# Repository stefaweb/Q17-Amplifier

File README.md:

# Q17 : A QUAD405 audiophile MOSFET amplifier
Q17 is an amplifier based on the QUAD405 current dumping principle.

The project for porting the operating principle of the QUAD405 to a MOSFET base was originally created by engineer Tiberiu Vicol.

Use KiCad to open and edit source files. The great KiCad software can be <a href="https://www.kicad.org/download/">downloaded</a> from CERN.

<b>Q17-Mini project 3.0 (90W @ 8 Ohms)</b>

The first version of the board was released on December 8, 2021.

Version 3.0.4 was published on October 7, 2024.

All files are located in Q17-Mini-3.0 directory. Old version are located in Q17-Mini Archives directory.

Q17-Mini v3.0 (95x75mm, 2 Oz PCB)

<b>Q17-TURBO project (150W @ 8 Ohms)</b>

The natural evolution of the Q17-Mini, this time with two pairs of power transistors, better thermal management, better technical characteristics and the same sound signature with more punch.

An amplifier that will warm up even the coldest speakers.

The first version of the board was released on January, 6 2023.

Version 2.0.1 was released on October 5, 2024.

All files are located in Q17-TURBO-2.0 directory. Old version are located in Q17-TURBO Archives directory.

Q17-TURBO v2.0 (190x75mm, 2 Oz PCB)

You can very simply manufacture your PCB via JLCPCB (https://jlcpcb.com) or PCBWay (https://www.pcbway.com) using the Gerber files available on this repository. You can also contact me, from time to time I have some spare copies of the Q17 PCBs that can be sold to you at cost price.

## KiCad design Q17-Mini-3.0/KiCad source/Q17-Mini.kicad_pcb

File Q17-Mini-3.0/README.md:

# Q17-Mini version 3.0 (90W @ 8 Ohms)</b><br>

<b>Technical specifications:</b>

THD: 0.011%<br>
SNR : 118 dB<br>
Intermodulation distortion: 0,2%<br>
Frequency response: ±0,1 dB<br>
Slew rate: 35 V/µs<br>
Damping factor : 350 with 1.2Vrms sensibility, 290 with 0.7Vrms sensibility<br>
Default gain: 22 with input gain at 1.2Vrms, 35 with input gain at 0.7Vrms.<br>
DC offset at output: 1mV with OPA1611, 0mV with OPA828.<br>
Power supply : 50Vdc<br>
Idle consumption: 9W

These measurements were made with amateur measuring equipment. It is better to take them as an indication than as safe values. 
<br>
<br>
The first version of the board was released on December 8, 2021.
<br>
<br>
Version 3.0.4 was published on October 7, 2024.

Read the CHANGELOG file to know what's new.

<a href="https://audio.cyberkata.org/Q17-Mini-3.0-BOM.html">Q17-Mini-3.0-BOM Online Version</a>
<br>
<br>
<a href="https://www.mouser.fr/ProjectManager/ProjectDetail.aspx?AccessID=dd2b71abab">Order Q17-Mini-3.0.4-BOM at Mouser</a><br> 
<br>

PCB size: 95 mm * 75 mm

Drilling for Q17-Mini

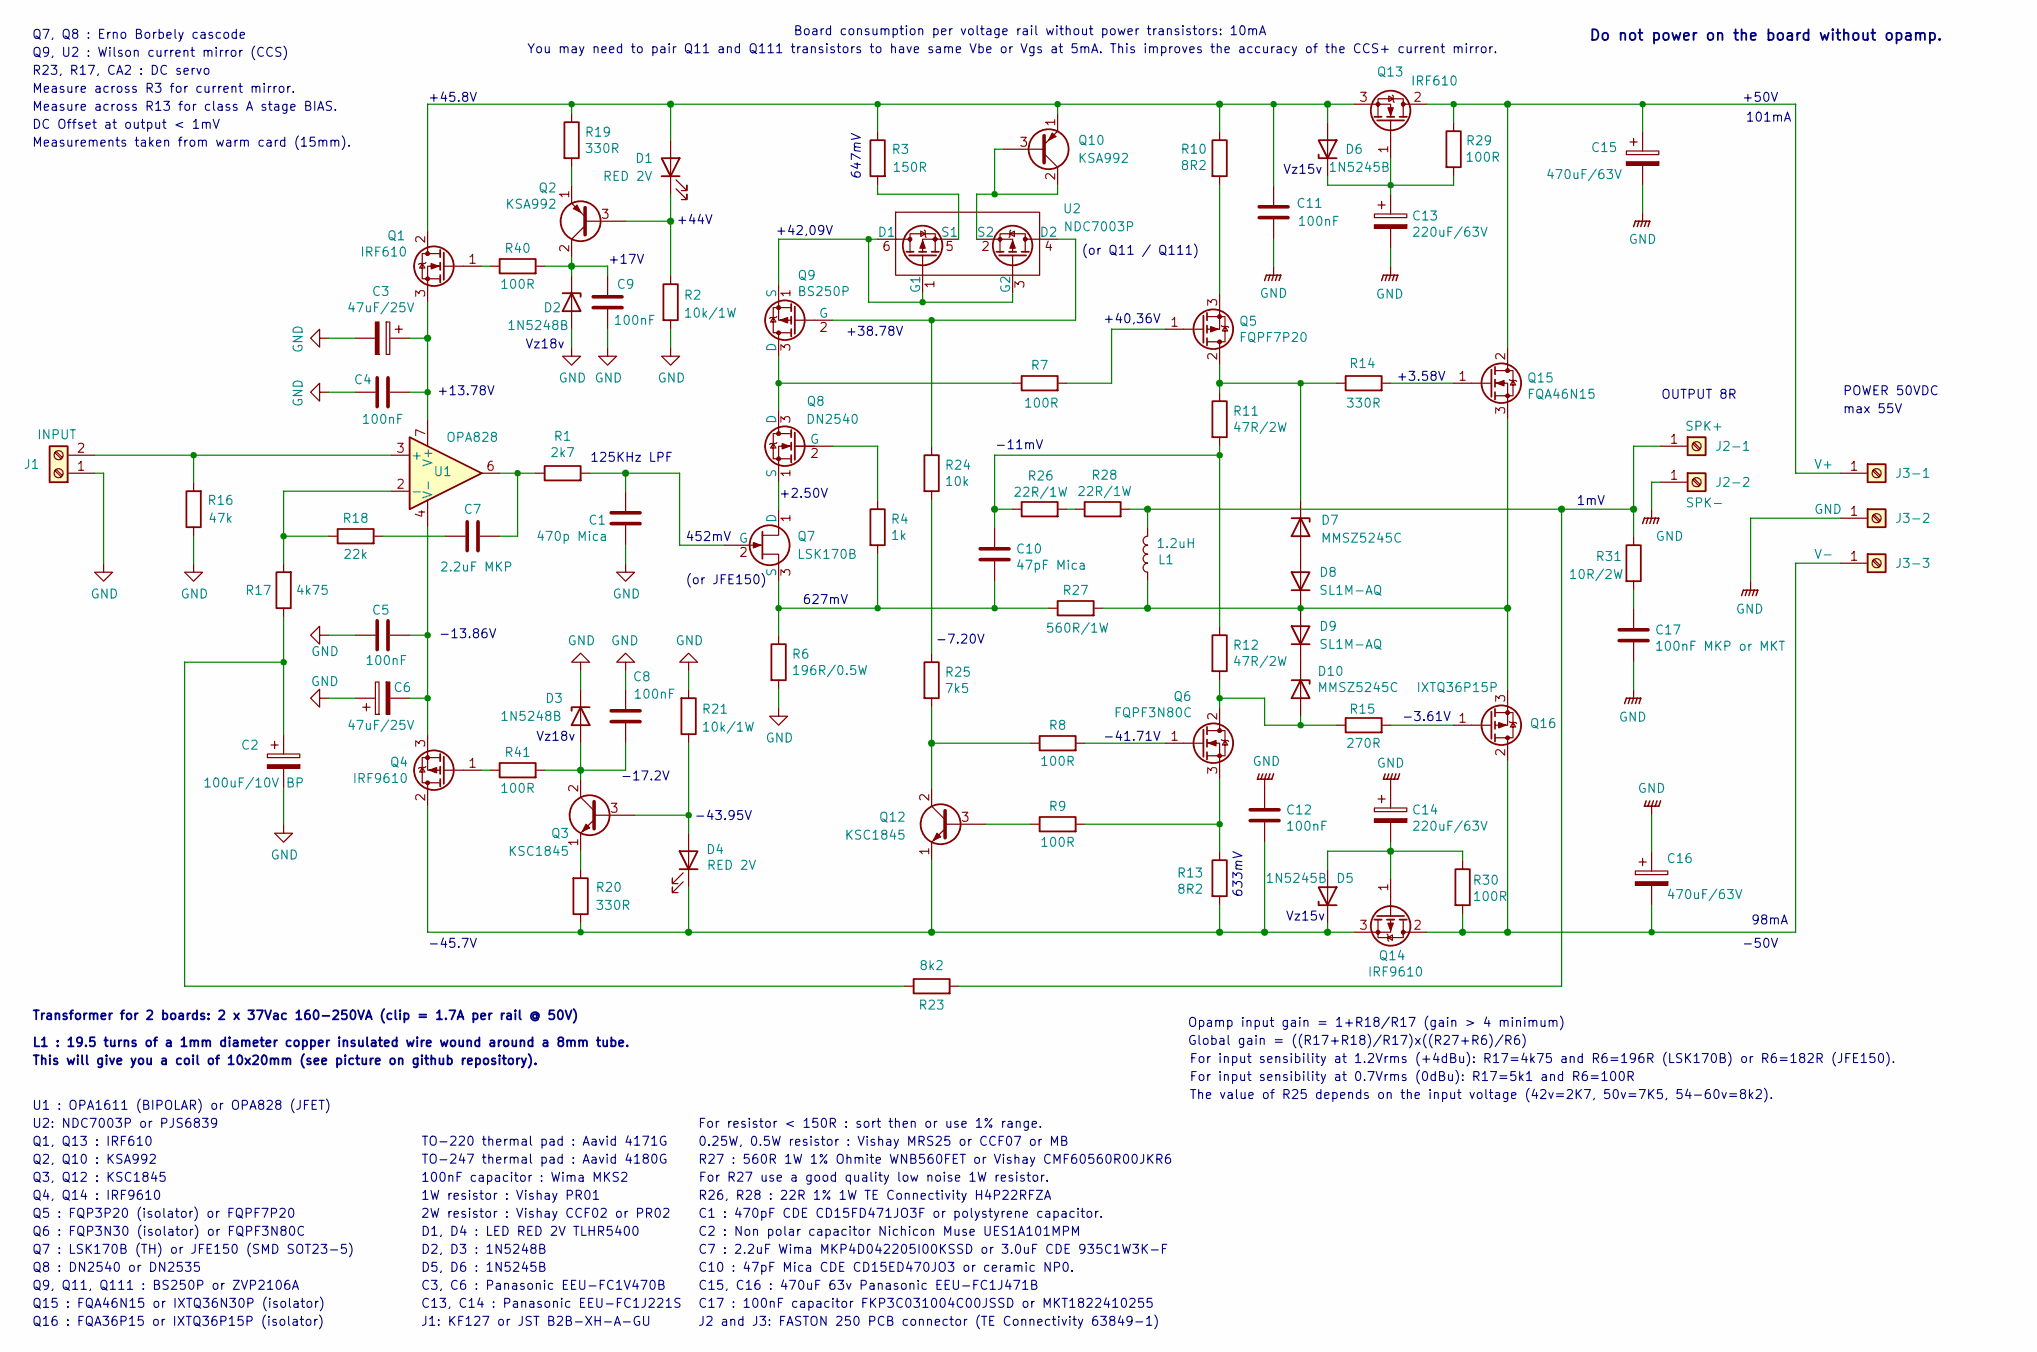
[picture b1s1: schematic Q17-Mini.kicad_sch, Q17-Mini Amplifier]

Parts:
C1: 470p Mica; C_Mica_v2_L11.4mm_W4.3mm_H9.1_P5.9mm_mix; Part# CD15FD471JO3; Mouser 5982-15-500V470
C2: 100uF/10V BP; CP_Radial_D10.0mm_P5.00mm; Part# UES1A101MPM; Mouser 647-UES1A101MPM
C3, C6: 47uF/25V; CP_Radial_D10.0mm_P2.50mm_P5.00mm; Part# EEU-FC1V470B; Mouser 667-EEU-FC1V470B
C4, C5, C8, C9, C11, C12: 100nF; C_Rect_L7.2mm_W2.5mm_P5.00mm_FKS2_FKP2_MKS2_MKP2; Part# MKS2D031001A00KSSD; Mouser 505-MKS2.1/100/10
C7: 2.2uF MKP; C_Rect_L26.5mm_W10.5mm_P22.50mm_MKS4; Part# MKP4D042205I00KSSD; Mouser 505-MKP4D042205I00KS
C10: 47pF Mica; C_Mica_v2_L11.4mm_W4.3mm_H9.1_P5.9mm_mix; Part# CD15ED470JO3F; Mouser 598-CD15ED470JO3F
C13, C14: 220uF/63V; CP_Radial_D12.5mm_P5.00mm; Part# EEU-FC1J221S; Mouser 667-EEU-FC1J221S
C15, C16: 470uF/63V; CP_Radial_D16.0mm_P7.50mm; Part# EEU-FC1J471B; Mouser 667-EEU-FC1J471B
C17: 100nF MKP or MKT; C_Rect_L18.0mm_W7.0mm_P15.00mm_FKS3_FKP3; Part# FKP3D031004D00JF00; Mouser 505-FKP3D03104D0JF0
D1, D4: RED 2V; LED_D5.0mm; Part# TLHR5400; Mouser 78-TLHR5400
D2, D3: 1N5248B; D_DO-35_SOD27_P7.62mm_Horizontal; Part# 1N5248B; Mouser 78-1N5248B
D5, D6: 1N5245B; D_DO-35_SOD27_P7.62mm_Horizontal; Part# 1N5245BTR; Mouser 512-1N5245BTR
D7, D10: MMSZ5245C; D_SOD-123; Part# MMSZ5245C-E3-18; Mouser 78-MMSZ5245C-E3-18
D8, D9: SL1M-AQ; D_SOD-123; Part# SL1M-AQ; Mouser 637-SL1M-AQ
J1: INPUT; Input_connector_mix_inverted; Part# Terminal Block Phoenix Contact 1755583; Mouser 651-1755583
J2-1: SPK+; Faston_Connector_63849-1_TEC; Part# TE Connectivity 63849-1; Mouser 571-638491
J2-2: SPK-; Faston_Connector_63849-1_TEC; Part# TE Connectivity 63849-1; Mouser 571-638491
J3-1: V+; Faston_Connector_63849-1_TEC; Part# TE Connectivity 63849-1; Mouser 571-638491
J3-2: GND; Faston_Connector_63849-1_TEC; Part# TE Connectivity 63849-1; Mouser 571-638491
J3-3: V-; Faston_Connector_63849-1_TEC; Part# TE Connectivity 63849-1; Mouser 571-638491
L1: 1.2uH; L_Axial_L22mm_D10mm_P21mm_vertical_Q17_Mini; Part# 19.5 turns of a 1mm diameter copper ins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; Mouser N.A
Q1, Q13: IRF610; TO-220-3_Vertical; Part# IRF610PBF; Mouser 844-IRF610PBF
Q2, Q10: KSA992; TO-92_Inline_Wide; Part# KSA992FTA; Mouser 512-KSA992FTA
Q3, Q12: KSC1845; TO-92_Inline_Wide; Part# KSC1845FTA; Mouser 512-KSC1845FTA
Q4, Q14: IRF9610; TO-220-3_Vertical; Part# IRF9610PBF; Mouser 844-IRF9610PBF
Q5: FQPF7P20; TO-220-3_Vertical; Part# FQPF7P20; Mouser 512-FQPF7P20
Q6: FQPF3N80C; TO-220-3_Vertical; Part# FQPF3N80C; Mouser 512-FQPF3N80C
Q7: LSK170B; TO-92_Inline_Wide; Part# LSK170B-TO-92-3L-BK; Mouser 722-LSK170BTO923LBK
Q8: DN2540; TO-92_Inline_Wide; Part# DN2540N3-G; Mouser 689-DN2540N3-G
Q9: BS250P; TO-92S_Wide; Part# BS250P; Mouser 522-BS250P
Q15: FQA46N15; TO-3P-3_Vertical; Part# FQA46N15; Mouser 512-FQA46N15
Q16: IXTQ36P15P; TO-3P-3_Vertical; Part# IXTQ36P15P; Mouser 747-IXTQ36P15P
R1: 2k7; R_Axial_DIN0207_L6.3mm_D2.5mm_P10.16mm_Horizontal; Part# MRS25000C2701FRP00; Mouser 594-MRS25000C2701FRP
R2, R21: 10k/1W; R_Axial_DIN0207_L6.3mm_D2.5mm_P10.16mm_Horizontal; Part# PR01000101002JR500; Mouser 594-5073NW10K00J
R3: 150R; R_Axial_DIN0207_L6.3mm_D2.5mm_P10.16mm_Horizontal; Part# MRS25000C1500FRP00; Mouser 594-MRS25000C1500FRP
R4: 1k; R_Axial_DIN0207_L6.3mm_D2.5mm_P10.16mm_Horizontal; Part# MRS25000C1001FRP00; Mouser 594-MRS25000C1001FRP
R6: 196R/0.5W; R_Axial_DIN0207_L6.3mm_D2.5mm_P10.16mm_Horizontal; Part# MRS25000C1960FCT00; Mouser 594-MRS25000C1960FCT
R7, R9, R29, R30, R40, R41: 100R; R_Axial_DIN0207_L6.3mm_D2.5mm_P10.16mm_Horizontal; Part# MRS25000C1000FCT00; Mouser 594-MRS25000C1000FCT
R8: 100R; R_Axial_DIN0207_L6.3mm_D2.5mm_P10.16mm_Horizontal; Part# MRS25000C1000FCT; Mouser 594-MRS25000C1000FCT
R10, R13: 8R2; R_Axial_DIN0207_L6.3mm_D2.5mm_P10.16mm_Horizontal; Part# MRS25000C8208FCT00; Mouser 594-MRS25000C8208FCT
R11, R12: 47R/2W; R_Axial_DIN0411_L9.9mm_D3.6mm_P12.70mm_Horizontal; Part# PR02000204709JR500; Mouser 594-5083NW47R00J
R14, R19, R20: 330R; R_Axial_DIN0207_L6.3mm_D2.5mm_P10.16mm_Horizontal; Part# MRS25000C3300FCT00; Mouser 594-MRS25000C3300FCT
R15: 270R; R_Axial_DIN0207_L6.3mm_D2.5mm_P10.16mm_Horizontal; Part# MRS25000C2700FCT00; Mouser 594-MRS25000C2700FCT
R16: 47k; R_Axial_DIN0207_L6.3mm_D2.5mm_P10.16mm_Horizontal; Part# MRS25000C4702FRP00; Mouser 594-MRS25000C4702FRP
R17: 4k75; R_Axial_DIN0207_L6.3mm_D2.5mm_P10.16mm_Horizontal; Part# MRS25000C4751FRP00; Mouser 594-MRS25000C4751FRP
R18: 22k; R_Axial_DIN0207_L6.3mm_D2.5mm_P10.16mm_Horizontal; Part# MRS25000C2202FCT00; Mouser 594-MRS25000C2202FCT
R23: 8k2; R_Axial_DIN0207_L6.3mm_D2.5mm_P10.16mm_Horizontal; Part# MRS25000C8201FRP00; Mouser 594-MRS25000C8201FRP
R24: 10k; R_Axial_DIN0207_L6.3mm_D2.5mm_P10.16mm_Horizontal; Part# MRS25000C1002FRP00; Mouser 594-MRS2510K00F
R25: 7k5; R_Axial_DIN0207_L6.3mm_D2.5mm_P10.16mm_Horizontal; Part# MRS25000C7501FRP00; Mouser 594-MRS25000C7501FRP
R26, R28: 22R/1W; R_Axial_DIN0411_L9.9mm_D3.6mm_P12.70mm_Horizontal; Part# H4P22RFZA; Mouser 279-H4P22RFZA
R27: 560R/1W; R_Axial_DIN0411_L9.9mm_D3.6mm_P12.70mm_Horizontal; Part# WNB560FET; Mouser 588-WNB560FET
R31: 10R/2W; R_Axial_DIN0411_L9.9mm_D3.6mm_P15.24mm_Horizontal; Part# PR02000201009JR500; Mouser 594-5083NW10R00J
U1: OPA828; SOIC-8_3.9x4.9mm_P1.27mm; Part# OPA828IDR; Mouser 595-OPA828IDR
U2: NDC7003P; NDC7003P-TSOT23-6; Part# NDC7003P; Mouser 512-NDC7003P

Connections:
GND: C1.2, C2.2, C3.2, C4.1, C5.1, C6.1, C8.1, C9.1, C11.1, C12.1, C13.2, C14.1, C15.2, C16.1, C17.2, D2.2 (A), D3.1 (K), J1.1, J2-2.1, J3-2.1, R2.2, R6.2, R16.1, R21.2; also elsewhere on the board
unnamed: C2.1, R17.1, R23.1
unnamed: C7.1, R18.2
unnamed 3: C7.2, R1.1, U1.6; also elsewhere on the board
unnamed: C10.1, R11.2, R12.1, R26.1
unnamed: C17.1, R31.2
unnamed 6: C11.2, D1.2 (A), D6.2 (A), Q1.2 (D), Q10.1 (E), Q13.3 (S), R3.1, R10.1, R19.1; also elsewhere on the board
unnamed: D1.1 (K), Q2.3 (B), R2.1
unnamed: C9.2, D2.1 (K), Q2.2 (C), R40.2
unnamed: C8.2, D3.2 (A), Q3.2 (C), R41.2
unnamed: D4.2 (A), Q3.3 (B), R21.1
unnamed 11: C12.2, D4.1 (K), D5.1 (K), Q4.2 (D), Q12.1 (E), Q14.3 (S), R13.2, R20.1; also elsewhere on the board
unnamed: C14.2, D5.2 (A), Q14.1 (G), R30.1
unnamed: C13.1, D6.1 (K), Q13.1 (G), R29.2
unnamed: D7.2 (A), D8.2 (A)
unnamed: D7.1 (K), Q5.2 (D), R11.1, R14.1
unnamed: D8.1 (K), D9.2 (A), L1.1, Q15.3 (S), Q16.3 (S), R27.2
unnamed: D10.2 (A), Q6.2 (D), R12.2, R15.1
unnamed: D9.1 (K), D10.1 (K)
unnamed 19: J1.2, R16.2, U1.3 (+); also elsewhere on the board
unnamed: J2-1.1, L1.2, R23.2, R28.2, R31.1
unnamed: C15.1, J3-1.1, Q13.2 (D), Q15.2 (D), R29.1
unnamed: C16.2, J3-3.1, Q14.2 (D), Q16.2 (D), R30.2
unnamed 23: Q1.1 (G), R40.1; also elsewhere on the board
unnamed 24: C3.1, C4.2, Q1.3 (S), U1.7 (V+); also elsewhere on the board
unnamed: Q2.1 (E), R19.2
unnamed: Q3.1 (E), R20.2
unnamed 27: Q4.1 (G), R41.1; also elsewhere on the board
unnamed 28: C5.2, C6.2, Q4.3 (S), U1.4 (V-); also elsewhere on the board
unnamed: Q5.1 (G), R7.2
unnamed: Q5.3 (S), R10.2
unnamed: Q6.1 (G), R8.2
unnamed: Q6.3 (S), R9.2, R13.1
unnamed 33: Q7.1 (D), Q8.1 (S); also elsewhere on the board
unnamed 34: C1.1, Q7.2 (G), R1.2; also elsewhere on the board
unnamed 35: C10.2, Q7.3 (S), R4.2, R6.1, R27.1; also elsewhere on the board
unnamed: Q8.3 (D), Q9.3 (D), R7.1
unnamed: Q8.2 (G), R4.1
unnamed 38: Q9.2 (G), R24.1, U2.4 (D2); also elsewhere on the board
unnamed 39: Q9.1 (S), U2.1 (G1), U2.3 (G2), U2.6 (D1); also elsewhere on the board
unnamed 40: Q10.2 (C), Q10.3 (B), U2.2 (S2); also elsewhere on the board
unnamed: Q12.3 (B), R9.1
unnamed: Q12.2 (C), R8.1, R25.2
unnamed: Q15.1 (G), R14.2
unnamed: Q16.1 (G), R15.2
unnamed: R24.2, R25.1
unnamed: R26.2, R28.1
unnamed 47: R17.2, R18.1, U1.2 (-); also elsewhere on the board
unnamed 48: R3.2, U2.5 (S1); also elsewhere on the board

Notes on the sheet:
-43.95V
Q15 : FQA46N15 or IXTQ36N30P (isolator)
452mV
+2.50V
max 55V
-17.2V
The value of R25 depends on the input voltage (42v=2K7, 50v=7K5, 54-60v=8k2).
1W resistor : Vishay PR01
-11mV
Q3, Q12 : KSC1845
-50V
U2: NDC7003P or PJS6839
This will give you a coil of 10x20mm (see picture on github repository).
-3.61V
Q5 : FQP3P20 (isolator) or FQPF7P20
+45.8V
125KHz LPF
R26, R28 : 22R 1% 1W TE Connectivity H4P22RFZA
627mV
TO-247 thermal pad : Aavid 4180G
(or JFE150)
Q1, Q13 : IRF610
D5, D6 : 1N5245B
C2 : Non polar capacitor Nichicon Muse UES1A101MPM
D2, D3 : 1N5248B
D1, D4 : LED RED 2V TLHR5400
For input sensibility at 0.7Vrms (0dBu): R17=5k1 and R6=100R
C3, C6 : Panasonic EEU-FC1V470B
J1: KF127 or JST B2B-XH-A-GU
U1 : OPA1611 (BIPOLAR) or OPA828 (JFET)
-7.20V
Board consumption per voltage rail without power transistors: 10mA
+3.58V
Q8 : DN2540 or DN2535
L1 : 19.5 turns of a 1mm diameter copper insulated wire wound around a 8mm tube.
Global gain = ((R17+R18)/R17)x((R27+R6)/R6)
Q6 : FQP3N30 (isolator) or FQPF3N80C
Q9, U2 : Wilson current mirror (CCS)
Transformer for 2 boards: 2 x 37Vac 160-250VA (clip = 1.7A per rail @ 50V)
For resistor < 150R : sort then or use 1% range.

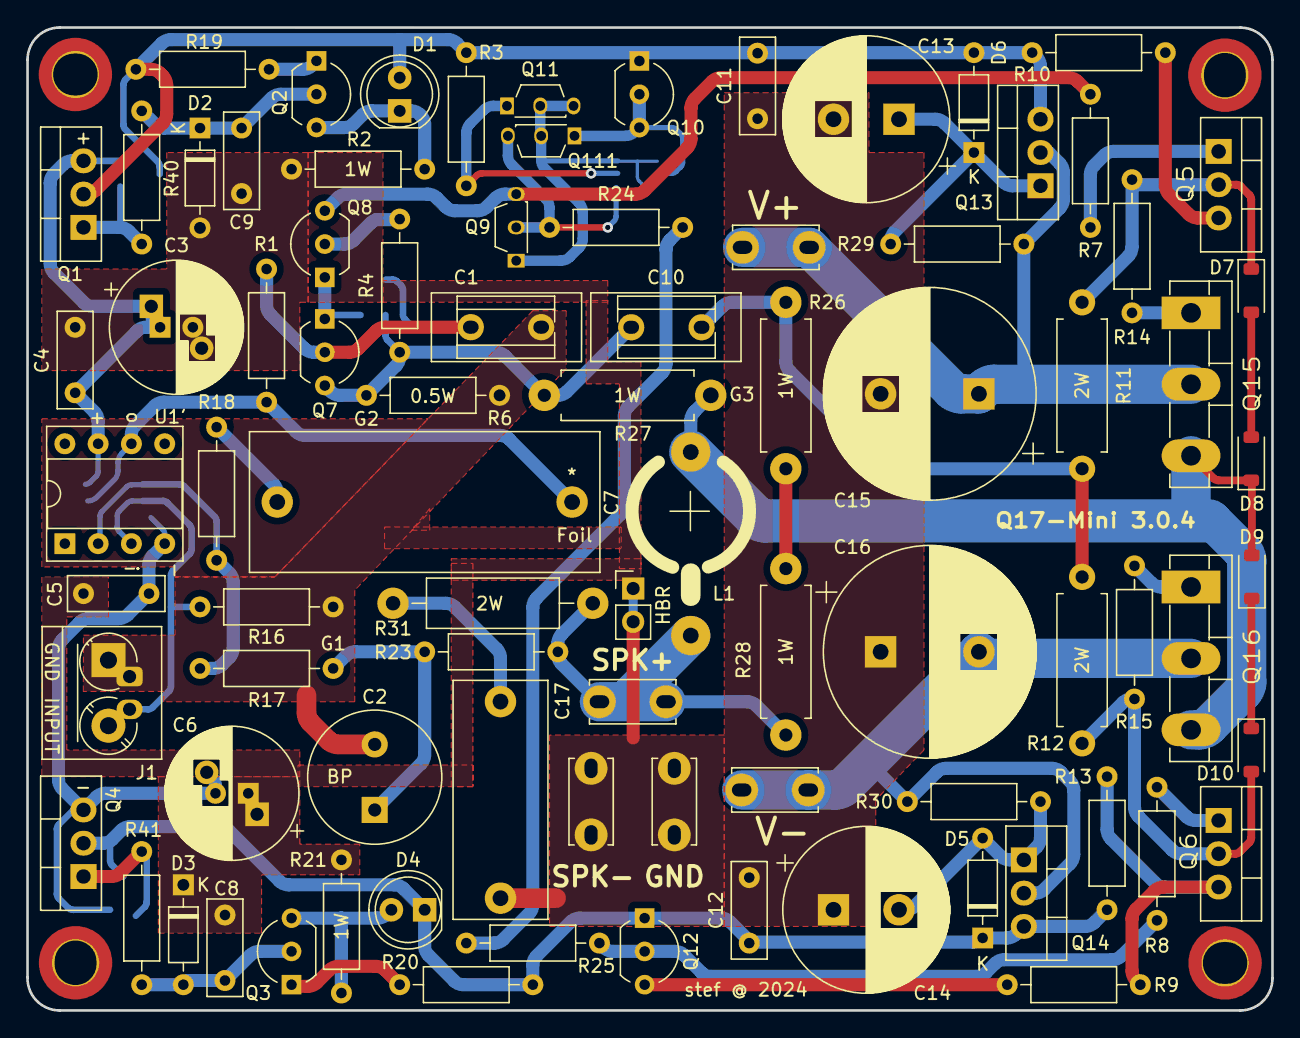
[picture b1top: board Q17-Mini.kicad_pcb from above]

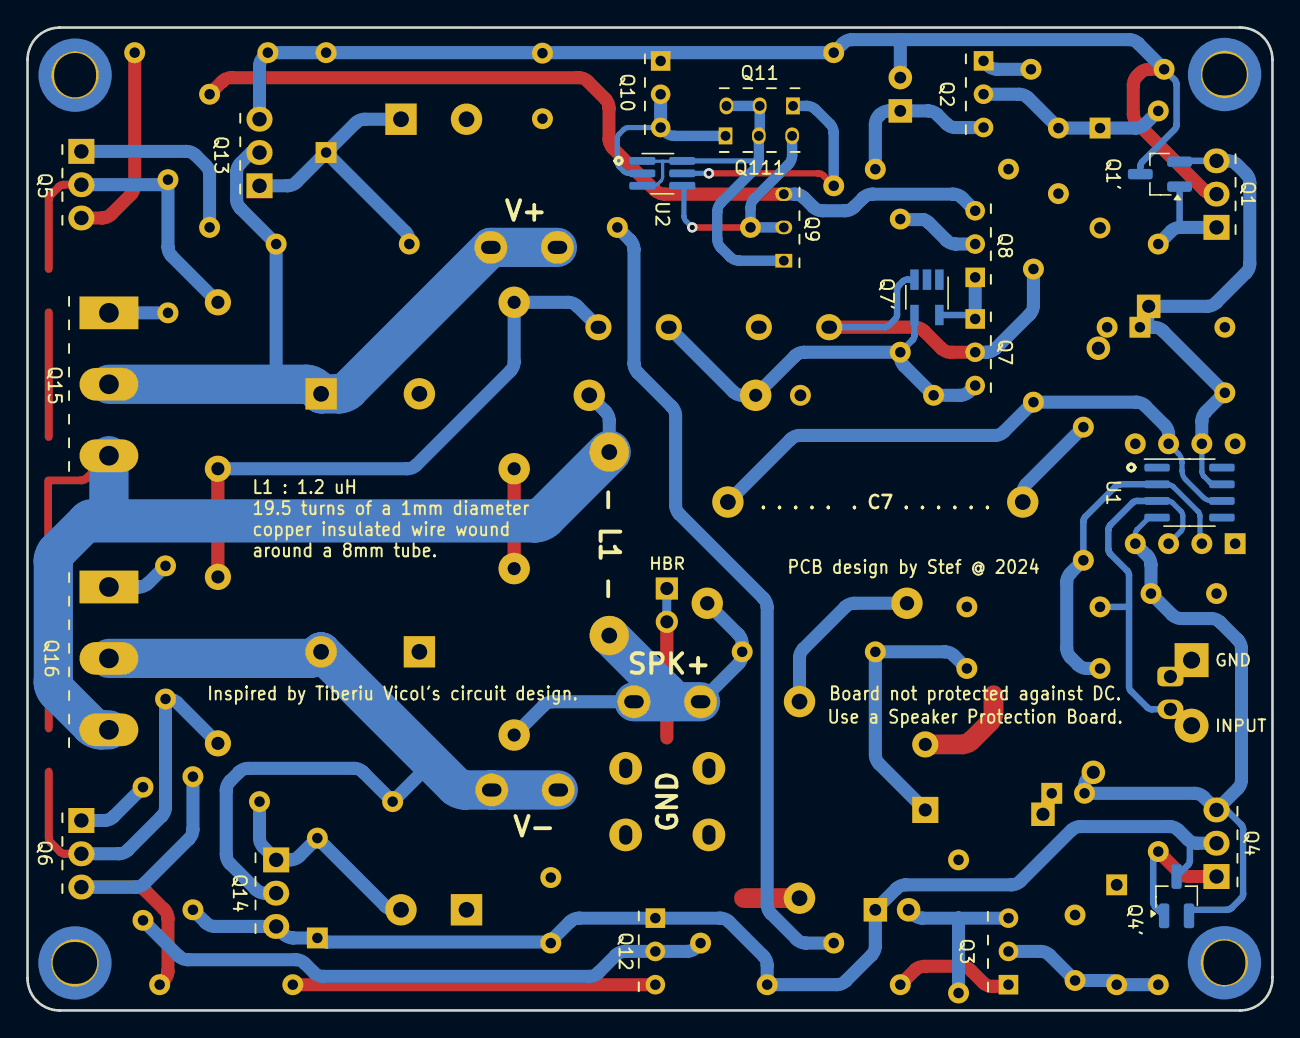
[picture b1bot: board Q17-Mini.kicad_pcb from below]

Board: 2 copper layers, 95.0 x 75.0 mm, 93 parts (5 on the bottom side), 49 nets.

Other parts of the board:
H1, H2, H4: MountingHole; MountingHole_3.2mm_M3_DIN965_Pad_TopBottom
H3: MountingHole_3.2mm_M3_DIN965_Pad_TopBottom
HBR: PinHeader_1x02_P2.54mm_Vertical
Q1': SI2328DS; SOT-23_Handsoldering
Q4': SI2325DS; SOT-23_Handsoldering
Q7': JFE150; SOT-23-5_HandSoldering
Q11, Q111: BS250P; TO-92S_Wide
U1': OPA828; DIP-8_W7.62mm_Socket

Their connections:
GND: HBR.1, HBR.2; also elsewhere on the board
unnamed 3: U1'.6; also elsewhere on the board
unnamed 6: Q1'.3; also elsewhere on the board
unnamed 11: Q4'.3; also elsewhere on the board
unnamed 19: U1'.3 (+); also elsewhere on the board
unnamed 23: Q1'.1; also elsewhere on the board
unnamed 24: Q1'.2, U1'.7 (V+); also elsewhere on the board
unnamed 27: Q4'.1; also elsewhere on the board
unnamed 28: Q4'.2, U1'.4 (V-); also elsewhere on the board
unnamed 33: Q7'.5; also elsewhere on the board
unnamed 34: Q7'.3; also elsewhere on the board
unnamed 35: Q7'.4; also elsewhere on the board
unnamed 38: Q111.3 (D); also elsewhere on the board
unnamed 39: Q11.2 (G), Q11.3 (D), Q111.2 (G); also elsewhere on the board
unnamed 40: Q111.1 (S); also elsewhere on the board
unnamed 47: U1'.2 (-); also elsewhere on the board
unnamed 48: Q11.1 (S); also elsewhere on the board

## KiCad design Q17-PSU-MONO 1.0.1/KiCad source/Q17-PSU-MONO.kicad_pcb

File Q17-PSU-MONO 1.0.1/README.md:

# Q17-PSU-MONO version 1.0.1<br>

Universal mono bridge Power Supply for Class B amplifiers.

Version 1.0.1 published on August 8, 2024.

<a href="https://audio.cyberkata.org/Q17-PSU-MONO-BOM.html">Online Q17-PSU-MONO-BOM</a><br>

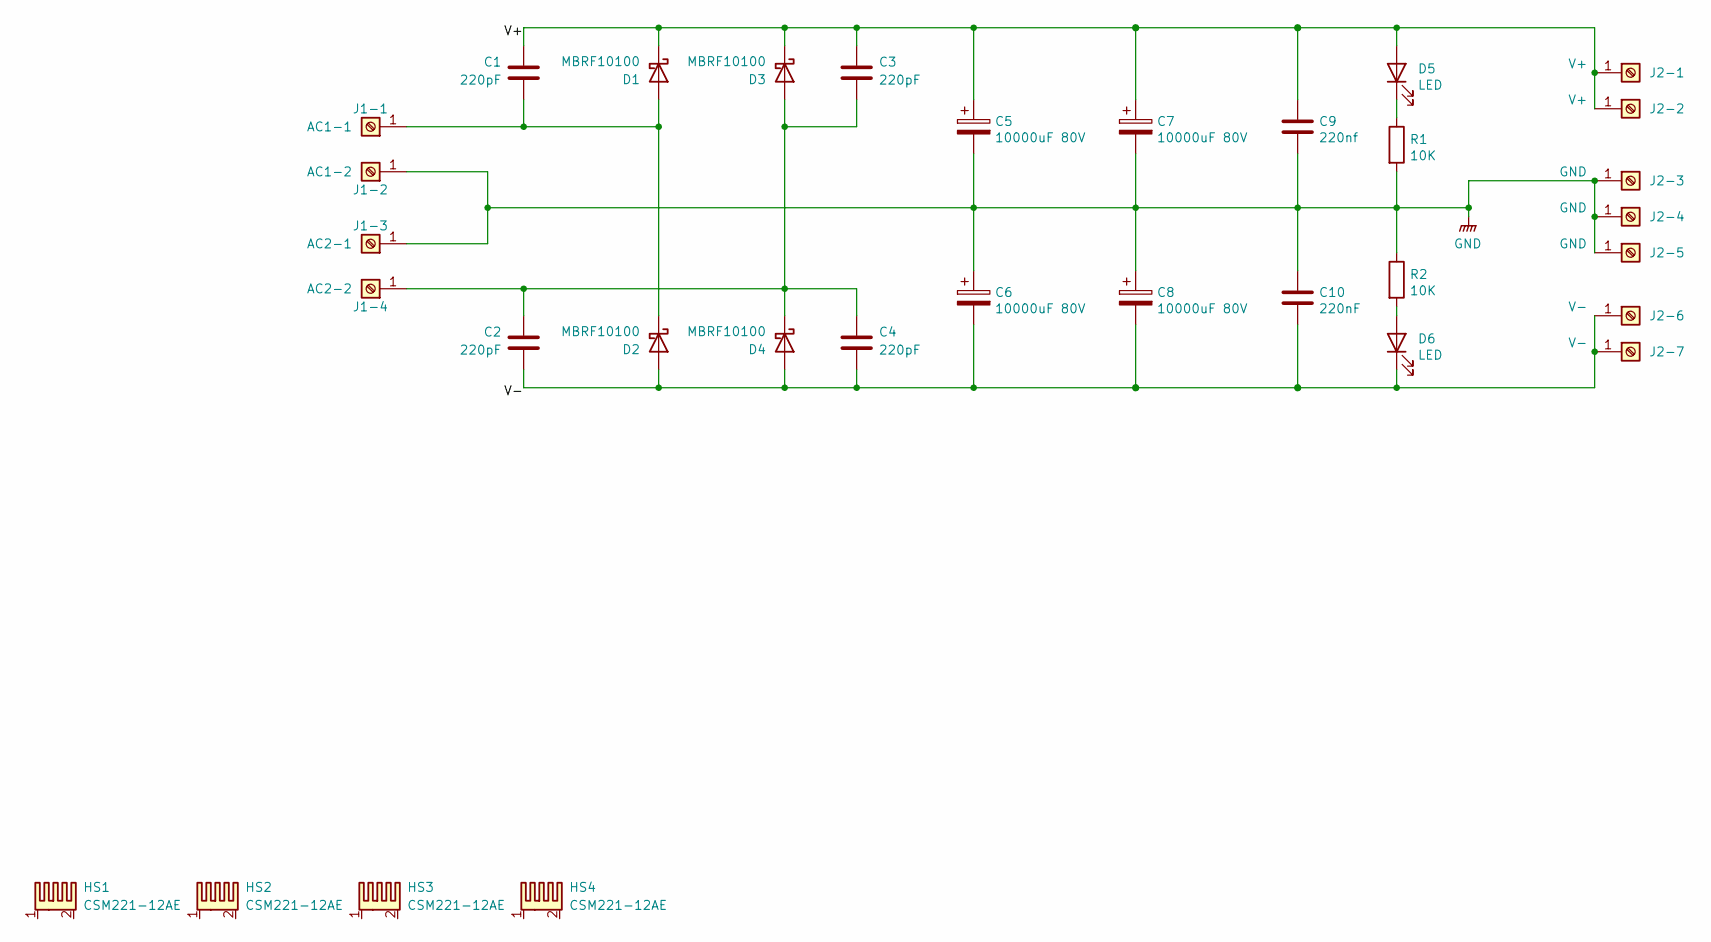
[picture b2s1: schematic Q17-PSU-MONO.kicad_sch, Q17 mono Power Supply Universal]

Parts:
C1, C2, C3, C4: 220pF; C_Disc_D6.0mm_W4.4mm_P5.00mm; Part# FG28C0G2A221JNT06; Mouser 810-FG28C0G2A221JNT6
C5, C6, C7, C8: 10000uF 80V; CP_Radial_D35.0mm_P10.00mm_SnapIn; Part# 380LX103M080A052; Mouser 598-380LX103M080A052
C9: 220nf; C_Rect_Q17_PSU_L26.50_H11.00_P20.50; Part# MPX224K305E; Mouser 598-MPX224K305E
C10: 220nF; C_Rect_Q17_PSU_L26.50_H11.00_P20.50; Part# MPX224K305E; Mouser 598-MPX224K305E
D1, D2, D3, D4: MBRF10100; TO-220-2_Vertical; Part# MBRF10100-M3/4W; Mouser 78-MBRF10100-M34W
D5, D6: LED; LED_D5.0mm; Part# TLHR5400; Mouser 78-TLHR5400
HS1, HS2, HS3, HS4: CSM221-12AE; CSM22112AE; Part# CSM221-12AE; Mouser 588-CSM221-12AE
J1-1: AC1-1; Faston_Connector_63849-1_TEC; Part# TE Connectivity 63849-1; Mouser 571-638241
J1-2: AC1-2; Faston_Connector_63849-1_TEC; Part# TE Connectivity 63849-1; Mouser 571-638241
J1-3: AC2-1; Faston_Connector_63849-1_TEC; Part# TE Connectivity 63849-1; Mouser 571-638241
J1-4: AC2-2; Faston_Connector_63849-1_TEC; Part# TE Connectivity 63849-1; Mouser 571-638241
J2-1, J2-2: V+; Faston_Connector_63849-1_TEC; Part# TE Connectivity 63849-1; Mouser 571-638241
J2-3, J2-4, J2-5: GND; Faston_Connector_63849-1_TEC; Part# TE Connectivity 63849-1; Mouser 571-638241
J2-6, J2-7: V-; Faston_Connector_63849-1_TEC; Part# TE Connectivity 63849-1; Mouser 571-638241
R1, R2: 10K; R_Axial_DIN0207_L6.3mm_D2.5mm_P10.16mm_Horizontal; Part# PR01000101002JR500; Mouser 594-5073NW10K00J

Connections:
/V+: C1.1, C3.1, C5.1, C7.1, C9.1, D1.1 (K), D3.1 (K), D5.2 (A), J2-1.1, J2-2.1
/V-: C2.2, C4.2, C6.2, C8.2, C10.2, D2.2 (A), D4.2 (A), D6.1 (K), J2-6.1, J2-7.1
GND: C5.2, C6.1, C7.2, C8.1, C9.2, C10.1, J1-2.1, J1-3.1, J2-3.1, J2-4.1, J2-5.1, R1.2, R2.1
unnamed: C1.2, D1.2 (A), D2.1 (K), J1-1.1
unnamed: C2.1, C3.2, C4.1, D3.2 (A), D4.1 (K), J1-4.1
unnamed: D5.1 (K), R1.1
unnamed: D6.2 (A), R2.2

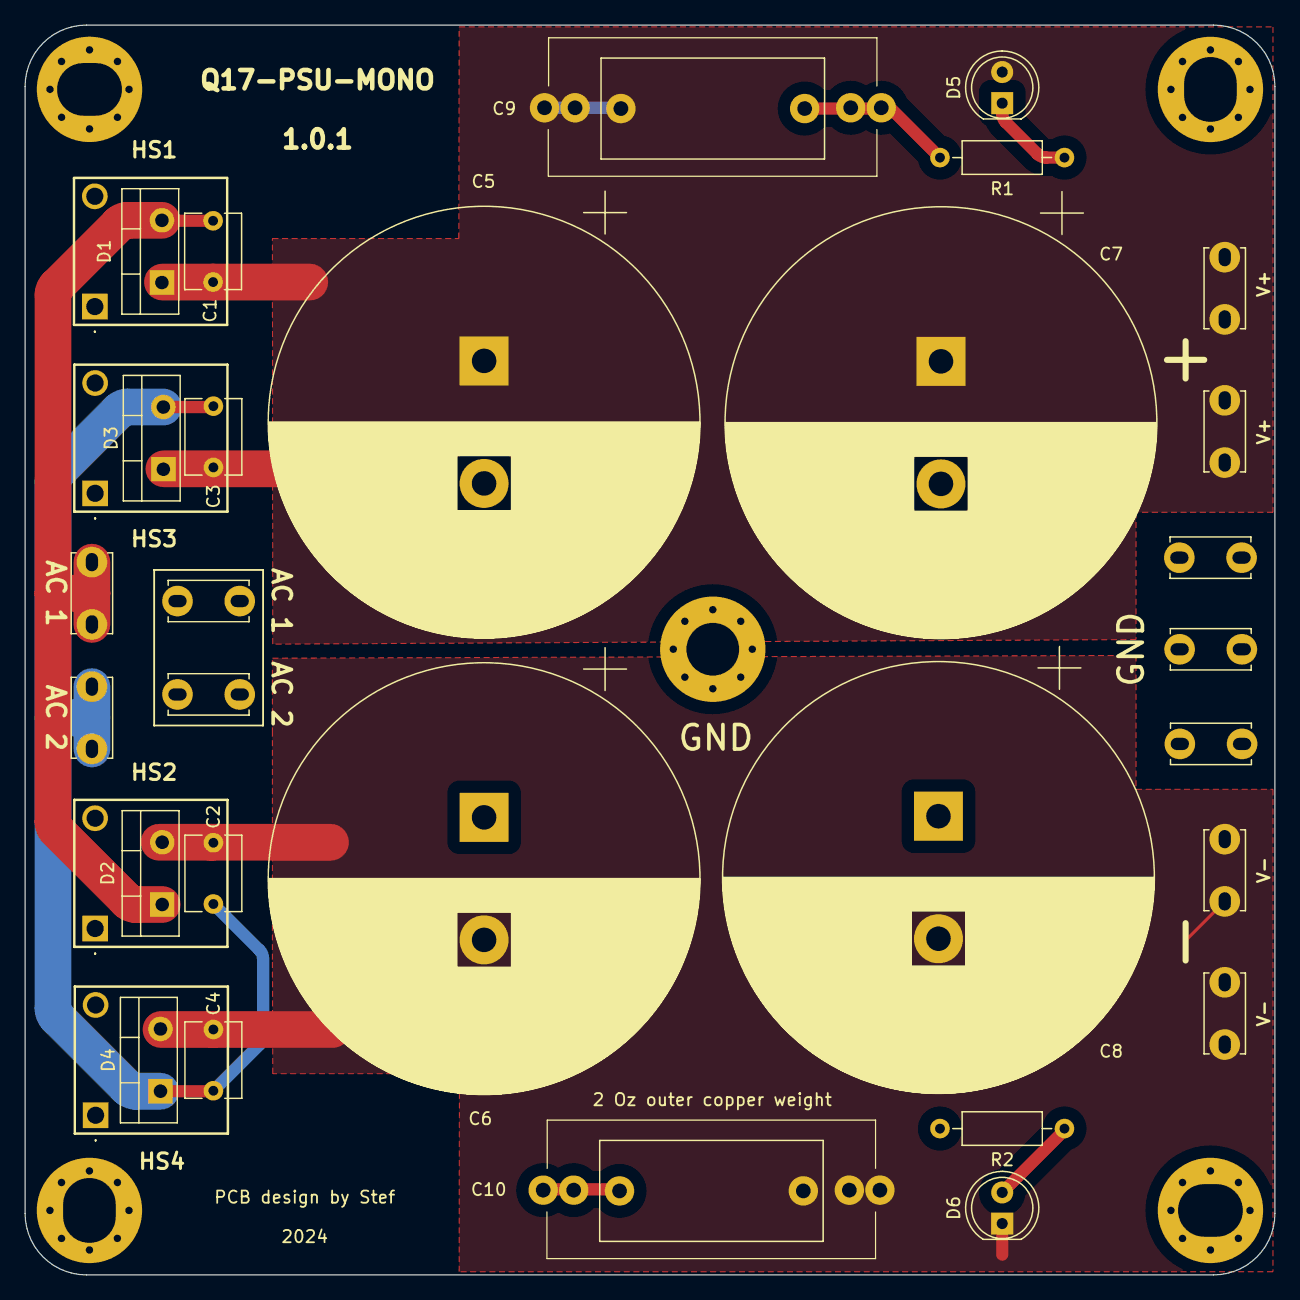
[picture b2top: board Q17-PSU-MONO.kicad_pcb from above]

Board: 2 copper layers, 102.0 x 102.0 mm, 33 parts (0 on the bottom side), 7 nets.

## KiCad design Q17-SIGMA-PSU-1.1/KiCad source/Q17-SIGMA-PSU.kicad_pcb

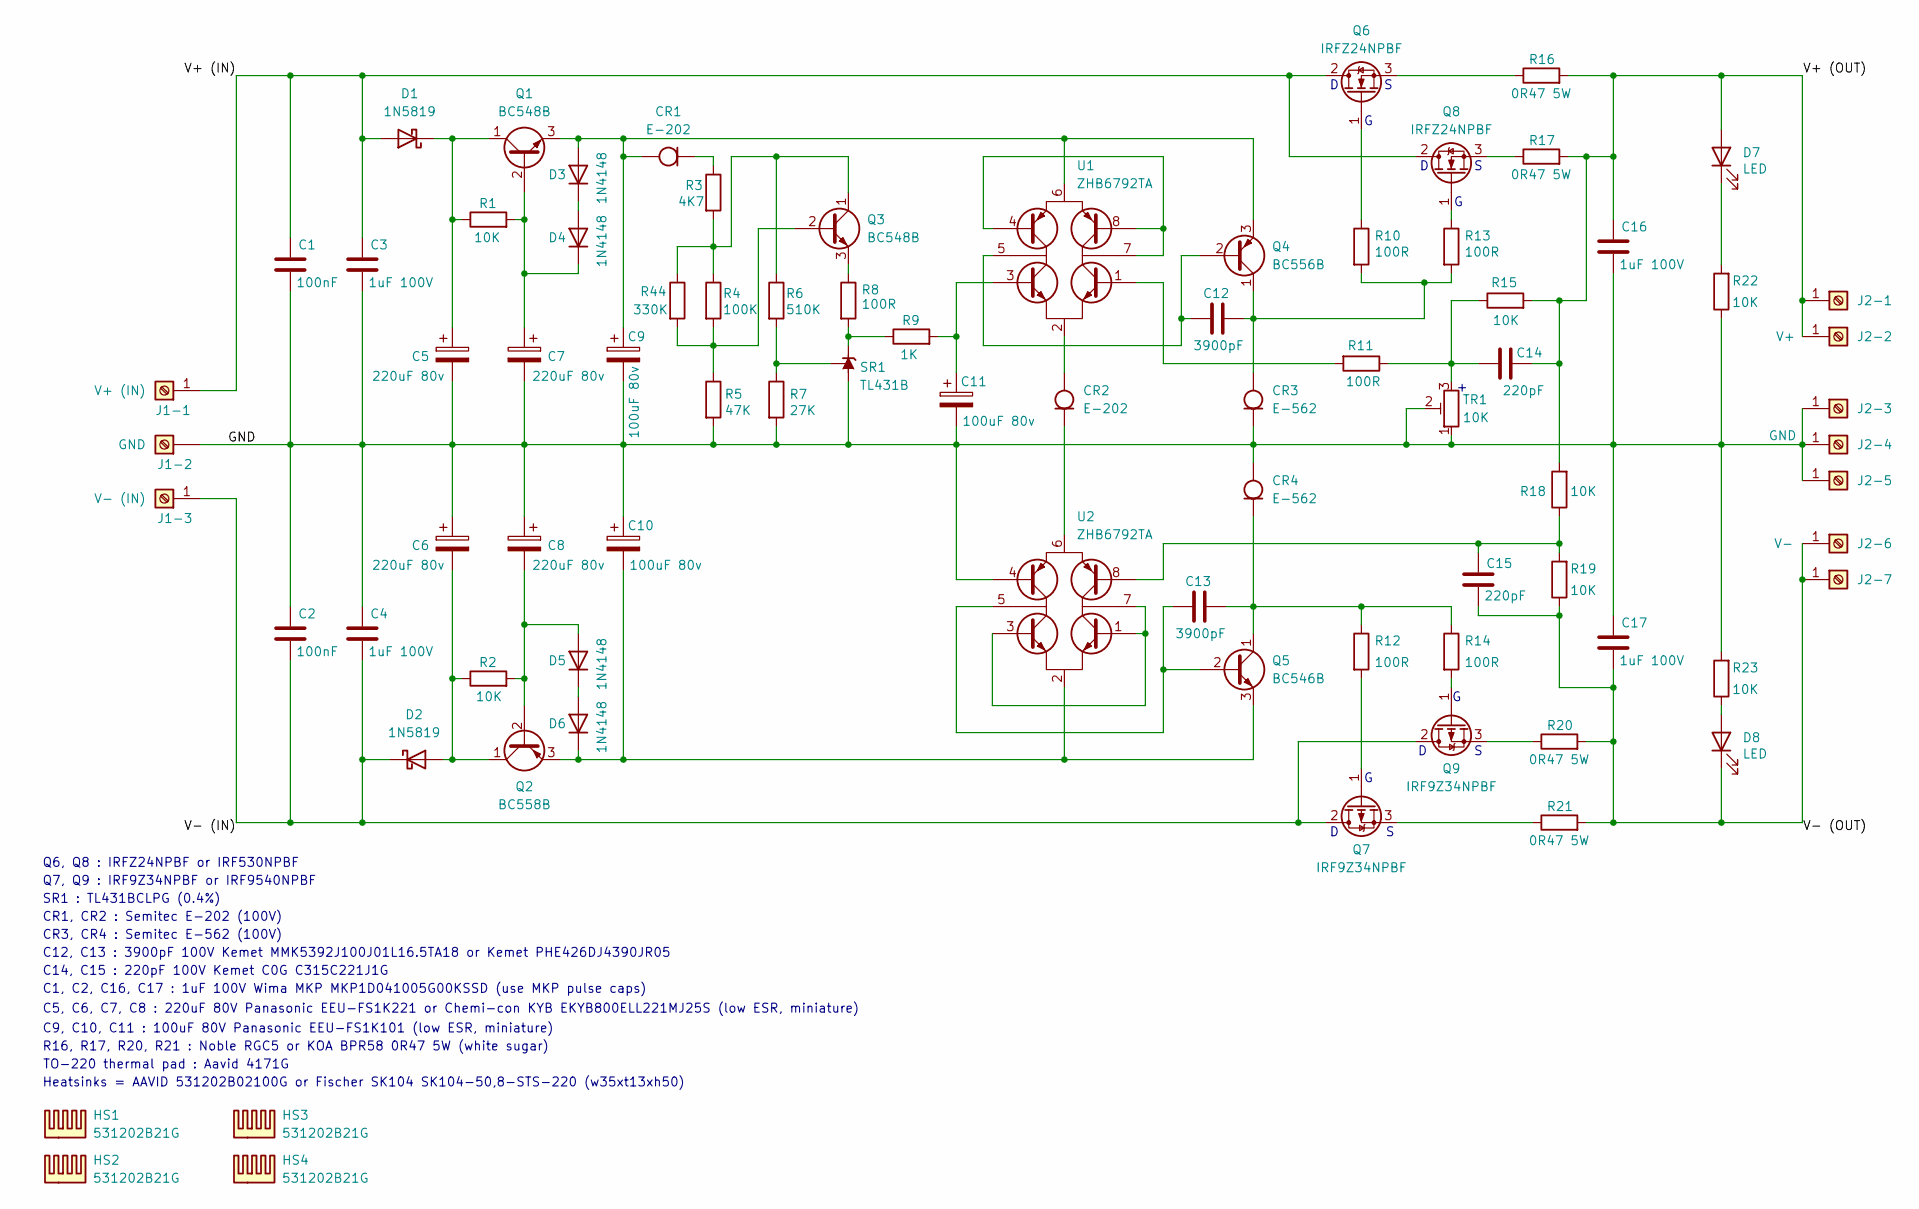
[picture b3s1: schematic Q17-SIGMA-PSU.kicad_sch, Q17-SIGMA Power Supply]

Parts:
C1, C2: 100nF; C_Rect_L7.2mm_W2.5mm_P5.00mm_FKS2_FKP2_MKS2_MKP2; Part# MKS2D031001A00KSSD; Mouser 505-MKS2.1/100/10
C3, C4, C16, C17: 1uF 100V; C_Rect_L26.5mm_W10.5mm_P22.50mm_MKS4; Part# MKP1D041005G00KSSD; Mouser 505-MKP1D041005G00KS
C5, C6, C7, C8: 220uF 80v; CP_Radial_D10.0mm_P5.00mm; Part# EEU-FS1K221; Mouser 667-EEU-FS1K221
C9, C10, C11: 100uF 80v; CP_Radial_D10.0mm_P5.00mm; Part# EEU-FS1K101; Mouser 667-EEU-FS1K101
C12, C13: 3900pF; C_Rect_L7.2mm_W2.5mm_P5.00mm_FKS2_FKP2_MKS2_MKP2; Part# MMK5392J100J01L16.5TA18; Mouser 80-MMK5392J100J1TA18
C14, C15: 220pF; C_Disc_D3.8mm_W2.6mm_P2.50mm; Part# C315C221J1G; Mouser 80-C315C221J1G
CR1, CR2: E-202; D_DO-35_SOD27_P7.62mm_Horizontal; Part# E-202; Mouser 954-E-202
CR3, CR4: E-562; D_DO-35_SOD27_P7.62mm_Horizontal; Part# E-562; Mouser 954-E-562
D1, D2: 1N5819; D_DO-41_SOD81_P10.16mm_Horizontal; Part# 1N5819-E3/73; Mouser 625-1N5819-E3/73
D3, D4, D5, D6: 1N4148; D_DO-35_SOD27_P7.62mm_Horizontal; Part# 1N4148-TAP; Mouser 78-1N4148-TAP
D7, D8: LED; LED_D5.0mm; Part# TLHR5400; Mouser 78-TLHR5400
HS1, HS2, HS3, HS4: 531202B21G; Heatsink_Fischer_SK104-STC-STIC_35x13mm_2xDrill2.5mm; Part# 531202B21G; Mouser 532-531202B21G
J1-1: V+ (IN); Faston_Connector_63849-1_TEC; Part# TE Connectivity 63849-1; Mouser 571-638241
J1-2, J2-3, J2-4, J2-5: GND; Faston_Connector_63849-1_TEC; Part# TE Connectivity 63849-1; Mouser 571-638241
J1-3: V- (IN); Faston_Connector_63849-1_TEC; Part# TE Connectivity 63849-1; Mouser 571-638241
J2-1, J2-2: V+; Faston_Connector_63849-1_TEC; Part# TE Connectivity 63849-1; Mouser 571-638241
J2-6, J2-7: V-; Faston_Connector_63849-1_TEC; Part# TE Connectivity 63849-1; Mouser 571-638241
Q1, Q3: BC548B; TO-92L_Inline_Wide; Part# BC548BTA; Mouser 512-BC548BTA
Q2: BC558B; TO-92L_Inline_Wide; Part# BC558B; Mouser 637-BC558B
Q4: BC556B; TO-92L_Inline_Wide; Part# BC556BTA; Mouser 512-BC556BTA
Q5: BC546B; TO-92L_Inline_Wide; Part# BC546BTA; Mouser 512-BC546BTA
Q6, Q8: IRFZ24NPBF; TO-220-3_Vertical; Part# IRFZ24NPBF; Mouser 942-IRFZ24NPBF
Q7, Q9: IRF9Z34NPBF; TO-220-3_Vertical; Part# IRF9Z34NPBF; Mouser 942-IRF9Z34NPBF
R1, R2, R15, R18, R19, R22, R23: 10K; R_Axial_DIN0207_L6.3mm_D2.5mm_P10.16mm_Horizontal; Part# MRS25000C1002FRP00; Mouser 594-MRS2510K00F
R3: 4K7; R_Axial_DIN0207_L6.3mm_D2.5mm_P10.16mm_Horizontal; Part# MRS25000C1009FRP00; Mouser 594-MRS25000C1009FRP
R4: 100K; R_Axial_DIN0207_L6.3mm_D2.5mm_P10.16mm_Horizontal; Part# MRS25000C1003FRP00; Mouser 594-MRS25000C1003FRP
R5: 47K; R_Axial_DIN0207_L6.3mm_D2.5mm_P10.16mm_Horizontal; Part# MRS25000C4702FRP00; Mouser 594-MRS25000C4702FRP
R6: 510K; R_Axial_DIN0207_L6.3mm_D2.5mm_P10.16mm_Horizontal; Part# MRS25000C5103FCT00; Mouser 594-MRS25000C5103FCT
R7: 27K; R_Axial_DIN0207_L6.3mm_D2.5mm_P10.16mm_Horizontal; Part# MRS25000C1009FRP00; Mouser 594-MRS25000C1009FRP
R8, R10, R11, R12, R13, R14: 100R; R_Axial_DIN0207_L6.3mm_D2.5mm_P10.16mm_Horizontal; Part# MRS25000C1000FRP00; Mouser 594-MRS25000C1000FRP
R9: 1K; R_Axial_DIN0207_L6.3mm_D2.5mm_P10.16mm_Horizontal; Part# MRS25000C1009FRP00; Mouser 594-MRS25000C1009FRP
R16, R17, R20, R21: 0R47 5W; R_Box_L14.0mm_W5.0mm_P9.00mm; Part# BPR58CR47J; Mouser 660-BPR58CR47J
R44: 330K; R_Axial_DIN0207_L6.3mm_D2.5mm_P10.16mm_Horizontal; Part# MRS25000C3303FCT00; Mouser 594-MRS25000C3303FCT
SR1: TL431B; TO-92L_Inline_Wide; Part# TL431BCLPG; Mouser 863-TL431BCLPG
TR1: 10K; Potentiometer_Bourns_3296W_Vertical; Part# 3296W-1-103LF; Mouser 652-3296W-1-103LF
U1, U2: ZHB6792TA; SOT-223-8; Part# ZHB6792TA; Mouser 522-ZHB6792TA

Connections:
/GND: C1.2, C2.1, C3.2, C4.1, C5.2, C6.1, C7.2, C8.1, C9.2, C10.1, C11.2, C16.2, C17.1, CR3.1 (K), CR4.2 (A), J1-2.1, J2-3.1, J2-4.1, J2-5.1, R5.2, R7.2, R22.1, R23.2, SR1.2 (A), TR1.1, TR1.2, U2.4 (B1)
/V+ (IN): C1.1, C3.1, D1.2 (A), J1-1.1, Q6.2 (D), Q8.2 (D)
/V+ (OUT): C14.2, C16.1, D7.2 (A), J2-1.1, J2-2.1, R15.2, R16.2, R17.2, R18.2
/V- (IN): C2.2, C4.2, D2.1 (K), J1-3.1, Q7.2 (D), Q9.2 (D)
/V- (OUT): C15.2, C17.2, D8.1 (K), J2-6.1, J2-7.1, R19.1, R20.2, R21.2
unnamed: C14.1, R11.1, R15.1, TR1.3
unnamed: C9.1, CR1.2 (A), D3.2 (A), Q1.3 (E), Q4.3 (E), U1.6 (E1,_E4)
unnamed: CR1.1 (K), R3.1
unnamed: CR2.2 (A), U1.2 (E2,_E3)
unnamed: CR2.1 (K), U2.6 (E1,_E4)
unnamed: C12.2, CR3.2 (A), Q4.1 (C), R10.2, R13.2
unnamed: C13.2, CR4.1 (K), Q5.1 (C), R12.1, R14.1
unnamed: C5.1, D1.1 (K), Q1.1 (C), R1.1
unnamed: C6.2, D2.2 (A), Q2.1 (C), R2.1
unnamed: D3.1 (K), D4.2 (A)
unnamed: C7.1, D4.1 (K), Q1.2 (B), R1.2
unnamed: C8.2, D5.2 (A), Q2.2 (B), R2.2
unnamed: D5.1 (K), D6.2 (A)
unnamed: C10.2, D6.1 (K), Q2.3 (E), Q5.3 (E), U2.2 (E2,_E3)
unnamed: D7.1 (K), R22.2
unnamed: D8.2 (A), R23.1
unnamed: Q3.2 (B), R4.2, R5.1, R44.2
unnamed: Q3.1 (C), R3.2, R4.1, R6.1, R44.1
unnamed: Q3.3 (E), R8.1
unnamed: C12.1, Q4.2 (B), U1.5 (C2,_C1)
unnamed: C13.1, Q5.2 (B), U2.5 (C2,_C1)
unnamed: Q6.1 (G), R10.1
unnamed: Q6.3 (S), R16.1
unnamed: Q7.1 (G), R12.2
unnamed: Q7.3 (S), R21.1
unnamed: Q8.1 (G), R13.1
unnamed: Q8.3 (S), R17.1
unnamed: Q9.1 (G), R14.2
unnamed: Q9.3 (S), R20.1
unnamed: R8.2, R9.1, SR1.3 (K)
unnamed: R6.2, R7.1, SR1.1 (REF)
unnamed: U1.4 (B1), U1.7 (C3,_C4), U1.8 (B4)
unnamed: C11.1, R9.2, U1.3 (B2)
unnamed: R11.2, U1.1 (B3)
unnamed: U2.1 (B3), U2.3 (B2), U2.7 (C3,_C4)
unnamed: C15.1, R18.1, R19.2, U2.8 (B4)

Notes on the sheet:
C5, C6, C7, C8 : 220uF 80V Panasonic EEU-FS1K221 or Chemi-con KYB EKYB800ELL221MJ25S (low ESR, miniature)
C1, C2, C16, C17 : 1uF 100V Wima MKP MKP1D041005G00KSSD (use MKP pulse caps)
SR1 : TL431BCLPG (0.4%)
C9, C10, C11 : 100uF 80V Panasonic EEU-FS1K101 (low ESR, miniature)
TO-220 thermal pad : Aavid 4171G
C12, C13 : 3900pF 100V Kemet MMK5392J100J01L16.5TA18 or Kemet PHE426DJ4390JR05
CR3, CR4 : Semitec E-562 (100V)
R16, R17, R20, R21 : Noble RGC5 or KOA BPR58 0R47 5W (white sugar)
Q7, Q9 : IRF9Z34NPBF or IRF9540NPBF
CR1, CR2 : Semitec E-202 (100V)
Q6, Q8 : IRFZ24NPBF or IRF530NPBF
C14, C15 : 220pF 100V Kemet C0G C315C221J1G
Heatsinks = AAVID 531202B02100G or Fischer SK104 SK104-50,8-STS-220 (w35xt13xh50)
